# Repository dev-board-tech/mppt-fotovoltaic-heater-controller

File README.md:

# MPPT Fotovoltaic Heater Controller
 A compact fotovoltaic high power high voltage MPPT heater controller

A very compact heater controller that uses fotovoltaic panels in order to heat water in a boiler.

The project is developed around an Arduino nano V3 module using a BW OLED 128x64 SPI or TWI display.

The controller is designed to be configured working in BUCK or BOST mode thru changing the location of three jumpers.

The BUCK/BOST coil can be mounted externally using screws, the same the PV input capacitor, this allow for the board to be more compact decreasing the production price.

Include:

* One fan PWM output.
* Two onboard digital temperature sensors DS18B20.
* One wired NTC 10K temperature sensor wired to the heater.
* Onboard voltage reference TL431LP.
* Dedicated current sensor ACS758xCB-100B-PFF.
* One temperature exceeded output terminal.
* One RTC with backup battery because the controller is powered exclusively from panels DS1307.
* UART connector with 5V power.
* TWI connector with 5V power.
* Support three models of dedicated AC-DC/DC-DC inverter 95-385V to 9-12V for powering the board from panels HLK-PM12/HLK-5M12/RAC04-12SGA.
* BUCK inverter from 9-12V to 15-18V to efficiently drive the gate of the power MOS/IGBT MC34063AD.

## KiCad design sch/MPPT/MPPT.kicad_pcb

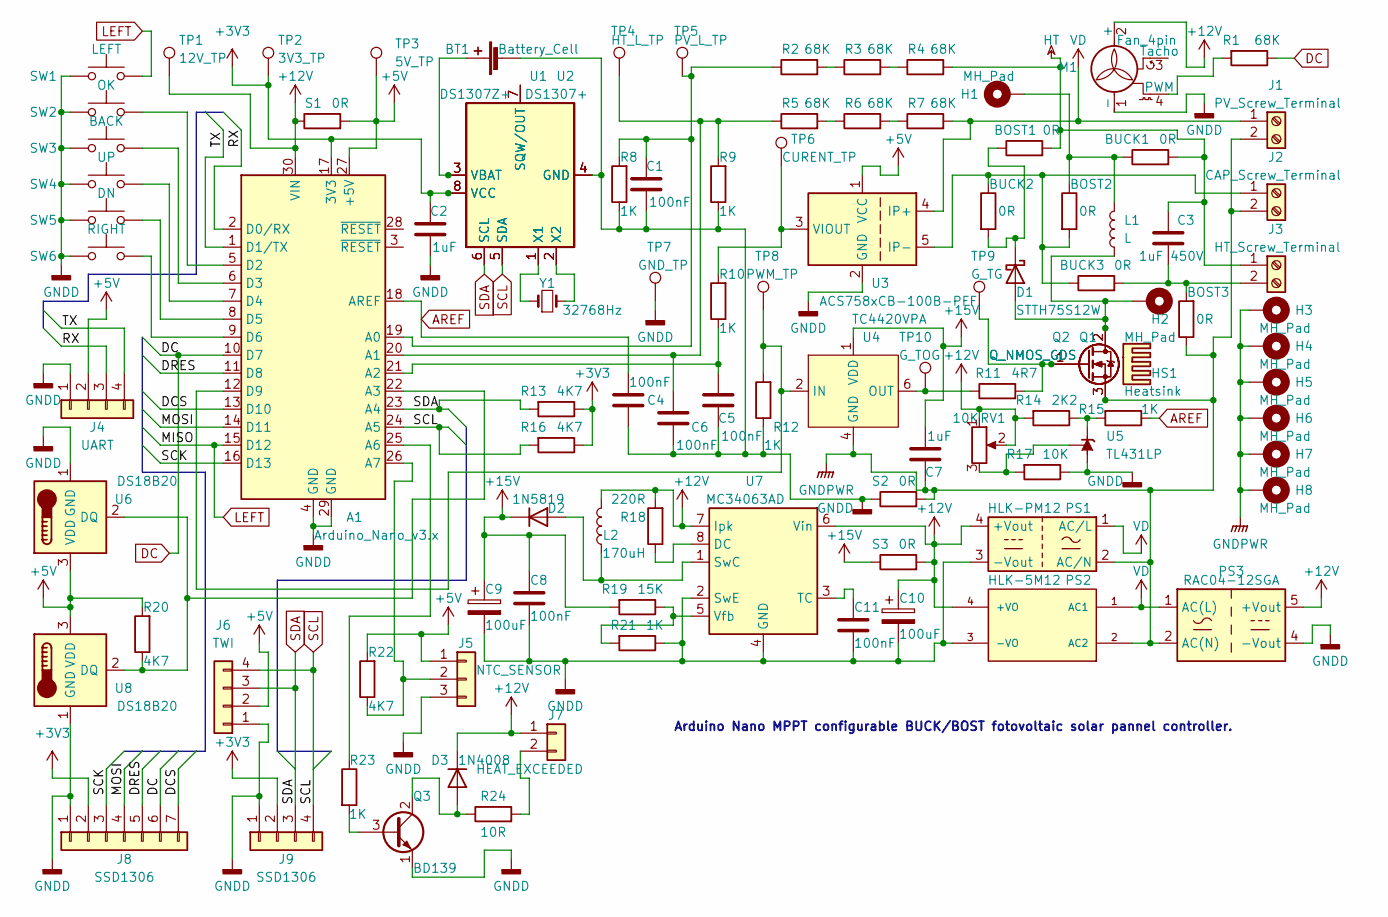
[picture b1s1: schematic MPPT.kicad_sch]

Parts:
A1: Arduino_Nano_v3.x; Arduino_Nano
BOST1, BOST2, BOST3: 0R; R_4020_10251Metric_Pad1.65x5.30mm_HandSolder
BT1: Battery_Cell; BatteryHolder_MPD_BC2003_1x2032
BUCK1, BUCK2, BUCK3: 0R; R_4020_10251Metric_Pad1.65x5.30mm_HandSolder
C1, C4, C5, C6, C8, C11: 100nF; C_0805_2012Metric_Pad1.18x1.45mm_HandSolder
C2: 1uF; C_0805_2012Metric_Pad1.18x1.45mm_HandSolder
C3: 1uF 450V; C_Rect_L27.0mm_W11.0mm_P22.00mm
C7: 1uF; C_1206_3216Metric_Pad1.33x1.80mm_HandSolder
C9, C10: 100uF; CP_Radial_D7.5mm_P2.50mm
D1: STTH75S12W; D_DO-247_Horizontal_TabDown
D2: 1N5819; D_A-405_P7.62mm_Horizontal
D3: 1N4008; D_A-405_P7.62mm_Horizontal
H1, H2, H3, H4, H5, H6, H7, H8: MH_Pad; MountingHole_3.2mm_M3_ISO14580_Pad_TopBottom
HS1: Heatsink; Heatsink_AAVID_TV5G_TO220_Horizontal
J1: PV_Screw_Terminal; TerminalBlock_MetzConnect_Type703_RT10N02HGLU_1x02_P9.52mm_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
J2: CAP_Screw_Terminal; TerminalBlock_MetzConnect_Type703_RT10N02HGLU_1x02_P9.52mm_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
J3: HT_Screw_Terminal; TerminalBlock_MetzConnect_Type703_RT10N02HGLU_1x02_P9.52mm_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
J4: UART; PinSocket_1x04_P2.54mm_Vertical
J5: NTC_SENSOR; TerminalBlock_bornier-3_P5.08mm
J6: TWI; PinSocket_1x04_P2.54mm_Vertical
J7: HEAT_EXCEEDED; TerminalBlock_bornier-2_P5.08mm
J8: SSD1306; PinSocket_1x07_P2.54mm_Vertical
J9: SSD1306; PinSocket_1x04_P2.54mm_Vertical
L1: L; HXX40A1.5uH
L2: 170uH; L_Radial_D10.0mm_P5.00mm_Fastron_07M
M1: Fan_4pin; Molex_SL_171971-0004_1x04_P2.54mm_Vertical
PS1: HLK-PM12; Converter_ACDC_HiLink_HLK-PMxx
PS2: HLK-5M12; CONV_HLK-5M05; PARTREV N/A
PS3: RAC04-12SGA; Converter_ACDC_RECOM_RAC04-xxSGx_THT
Q1, Q2: Q_NMOS_GDS; TO-247-3_Horizontal_TabDown
Q3: BD139; TO-126-3_Vertical
R1, R2, R3, R4, R5, R6, R7: 68K; R_1206_3216Metric_Pad1.30x1.75mm_HandSolder
R8, R9, R10, R12, R15, R21, R23: 1K; R_0805_2012Metric_Pad1.20x1.40mm_HandSolder
R11: 4R7; R_1206_3216Metric_Pad1.30x1.75mm_HandSolder
R13, R16, R20, R22: 4K7; R_0805_2012Metric_Pad1.20x1.40mm_HandSolder
R14: 2K2; R_0805_2012Metric_Pad1.20x1.40mm_HandSolder
R17: 10K; R_0805_2012Metric_Pad1.20x1.40mm_HandSolder
R18: 220R; R_0805_2012Metric_Pad1.20x1.40mm_HandSolder
R19: 15K; R_0805_2012Metric_Pad1.20x1.40mm_HandSolder
R24: 10R; R_Axial_DIN0204_L3.6mm_D1.6mm_P7.62mm_Horizontal
RV1: 10K; Potentiometer_Bourns_3296W_Vertical
S1, S2, S3: 0R; R_1206_3216Metric_Pad1.30x1.75mm_HandSolder
SW1: LEFT; SW_PUSH_6mm_H13mm
SW2: OK; SW_PUSH_6mm_H13mm
SW3: BACK; SW_PUSH_6mm_H13mm
SW4: UP; SW_PUSH_6mm_H13mm
SW5: DN; SW_PUSH_6mm_H13mm
SW6: RIGHT; SW_PUSH_6mm_H13mm
TP1: 12V_TP; TestPoint_THTPad_1.0x1.0mm_Drill0.5mm
TP2: 3V3_TP; TestPoint_THTPad_1.0x1.0mm_Drill0.5mm
TP3: 5V_TP; TestPoint_THTPad_1.0x1.0mm_Drill0.5mm
TP4: HT_L_TP; TestPoint_THTPad_1.0x1.0mm_Drill0.5mm
TP5: PV_L_TP; TestPoint_THTPad_1.0x1.0mm_Drill0.5mm
TP6: CURENT_TP; TestPoint_THTPad_1.0x1.0mm_Drill0.5mm
TP7: GND_TP; TestPoint_THTPad_1.0x1.0mm_Drill0.5mm
TP8: PWM_TP; TestPoint_THTPad_1.0x1.0mm_Drill0.5mm
TP9: G_TG; TestPoint_THTPad_1.0x1.0mm_Drill0.5mm
TP10: G_TOG; TestPoint_THTPad_1.0x1.0mm_Drill0.5mm
U1: DS1307+; DIP-8_W7.62mm
U2: DS1307Z+; SOIC-8_3.9x4.9mm_P1.27mm
U3: ACS758xCB-100B-PFF; Allegro_CB_PFF
U4: TC4420VPA; DIP-8_W7.62mm_LongPads
U5: TL431LP; TO-92_Inline
U6, U8: DS18B20; TO-92_Inline_Wide
U7: MC34063AD; SOIC-8_3.9x4.9mm_P1.27mm
Y1: 32768Hz; Crystal_AT310_D3.0mm_L10.0mm_Horizontal

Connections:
+3V3: A1.17 (3V3), C2.2, J8.2, J9.2, R13.1, R16.1, TP2.1, U1.8 (VCC), U2.8 (VCC)
+5V: A1.27 (+5V), J4.2, J5.1, J6.2, R20.2, R22.2, S1.2, TP3.1, U3.1 (VCC), U6.3 (VDD), U8.3 (VDD)
+12V: A1.30 (VIN), C10.1, D3.1 (K), J7.1, L2.2, M1.2 (+), PS1.4 (+Vout), PS2.4 (+VO), PS3.5 (+Vout), R14.2, R18.2, RV1.1, RV1.2, S1.1, S3.2, TP1.1, U7.6 (Vin), U7.7 (Ipk)
+15V: C7.2, C8.1, C9.1, D2.1 (K), R19.2, S3.1, U4.1 (VDD), U4.8 (VDD)
/DCS: A1.13 (D10), J8.7
/DRES: A1.11 (D8), J8.5
/MOSI: A1.14 (D11), J8.4
/RX: A1.2 (D0/RX), J4.3
/SCK: A1.16 (D13), J8.3
/TX: A1.1 (D1/TX), J4.4
AREF: A1.18 (AREF), C4.1, R15.1
DC: A1.10 (D7), J8.6, R1.1
GNDD: A1.4 (GND), A1.29 (GND), BT1.2 (-), C1.1, C2.1, C4.2, C5.1, C6.1, C8.2, C9.2, C10.2, C11.2, J4.1, J5.3, J6.1, J8.1, J9.1, M1.1 (-), PS1.3 (-Vout), PS2.3 (-VO), PS3.4 (-Vout), Q3.1 (E), R8.1, R9.1, R12.1, R17.1, R21.1, S2.1, SW1.1, SW2.1, SW3.1, SW4.1, SW5.1, SW6.1, TP7.1, U1.4 (GND), U2.4 (GND), U3.2 (GND), U5.2 (A), U6.1 (GND), U7.2 (SwE), U7.4 (GND), U8.1 (GND)
GNDPWR: BOST3.1, C7.1, H3.1, H4.1, H5.1, H6.1, H7.1, H8.1, J1.2, J2.2, PS1.2 (AC/N), PS2.2 (AC2), PS3.2 (AC(N)), Q1.3 (S), Q2.3 (S), S2.2, U4.4 (GND), U4.5 (GND)
HT: BOST1.2, BUCK1.2, C3.2, J3.1, R4.2
LEFT: A1.15 (D12), SW1.2
unnamed: A1.5 (D2), SW2.2
unnamed: A1.6 (D3), SW3.2
unnamed: A1.7 (D4), SW4.2
unnamed: A1.8 (D5), SW5.2
unnamed: A1.9 (D6), SW6.2
unnamed: A1.12 (D9), R12.2, TP8.1, U4.2 (IN)
unnamed: A1.19 (A0), C1.2, R2.1, R8.2, TP5.1
unnamed: A1.20 (A1), C6.2, R5.1, R9.2, TP4.1
unnamed: A1.21 (A2), C5.2, R10.1
unnamed: A1.22 (A3), R20.1, U6.2 (DQ), U8.2 (DQ)
unnamed: A1.25 (A6), R23.1
unnamed: A1.26 (A7), J5.2, R22.1
unnamed: BOST1.1, BUCK2.2, D1.1 (K)
unnamed: BOST2.1, BUCK1.1, H1.1, L1.2
unnamed: BOST2.2, BUCK2.1, BUCK3.1, J2.1, U3.5 (IP-)
unnamed: BOST3.2, BUCK3.2, C3.1, J3.2
unnamed: BT1.1 (+), U1.3 (VBAT), U2.3 (VBAT)
unnamed: C11.1, U7.3 (TC)
unnamed: D1.2 (A), H2.1, L1.1, Q1.2 (D), Q2.2 (D)
unnamed: D2.2 (A), L2.1, U7.1 (SwC)
unnamed: D3.2 (A), Q3.2 (C), R24.1
unnamed: J7.2, R24.2
unnamed: M1.4 (PWM), R1.2
unnamed: Q1.1 (G), Q2.1 (G), R11.2, TP9.1
unnamed: Q3.3 (B), R23.2
unnamed: R2.2, R3.1
unnamed: R3.2, R4.1
unnamed: R5.2, R6.1
unnamed: R6.2, R7.1
unnamed: R10.2, TP6.1, U3.3 (VIOUT)
unnamed: R11.1, TP10.1, U4.6 (OUT), U4.7 (OUT)
unnamed: R14.1, R15.2, U5.3 (K)
unnamed: R17.2, RV1.3, U5.1 (REF)
unnamed: R18.1, U7.8 (DC)
unnamed: R19.1, R21.2, U7.5 (Vfb)
unnamed: U1.1 (X1), U2.1 (X1), Y1.1
unnamed: U1.2 (X2), U2.2 (X2), Y1.2
unnamed: U1.7 (SQW/OUT), U2.7 (SQW/OUT)
SCL: A1.24 (A5), J6.4, J9.4, R16.2, U1.5 (SDA), U2.5 (SDA)
SDA: A1.23 (A4), J6.3, J9.3, R13.2, U1.6 (SCL), U2.6 (SCL)
VD: J1.1, PS1.1 (AC/L), PS2.1 (AC1), PS3.1 (AC(L)), R7.2, U3.4 (IP+)

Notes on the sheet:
Arduino Nano MPPT configurable BUCK/BOST fotovoltaic solar pannel controller.

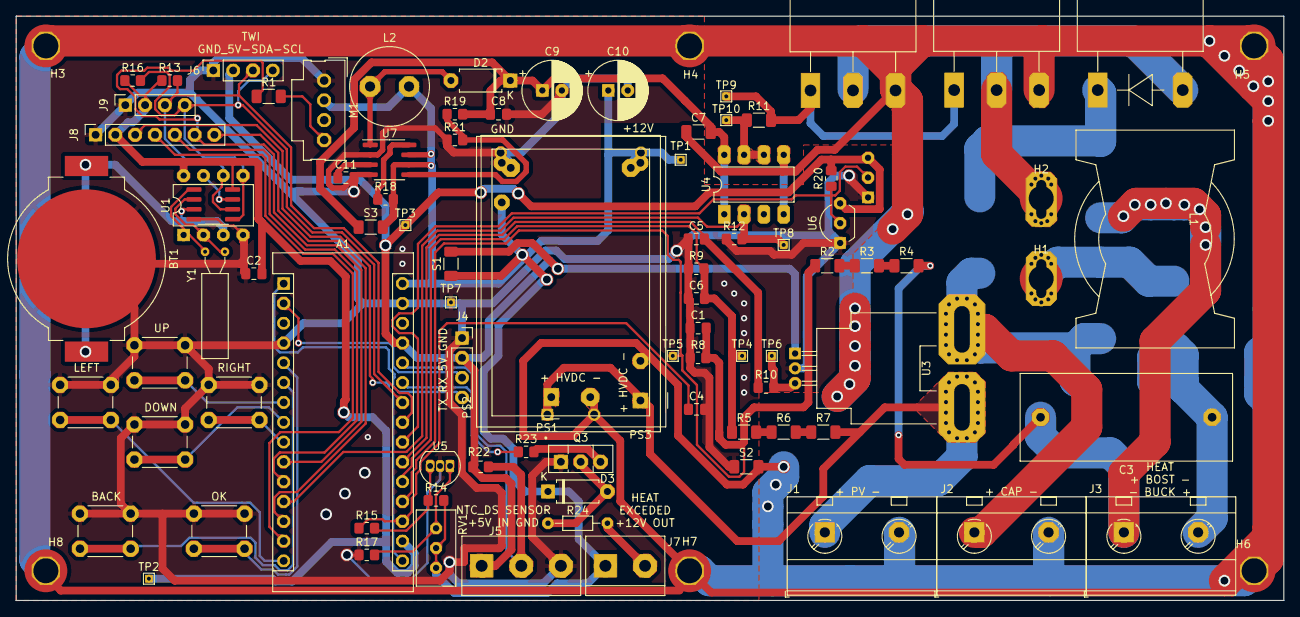
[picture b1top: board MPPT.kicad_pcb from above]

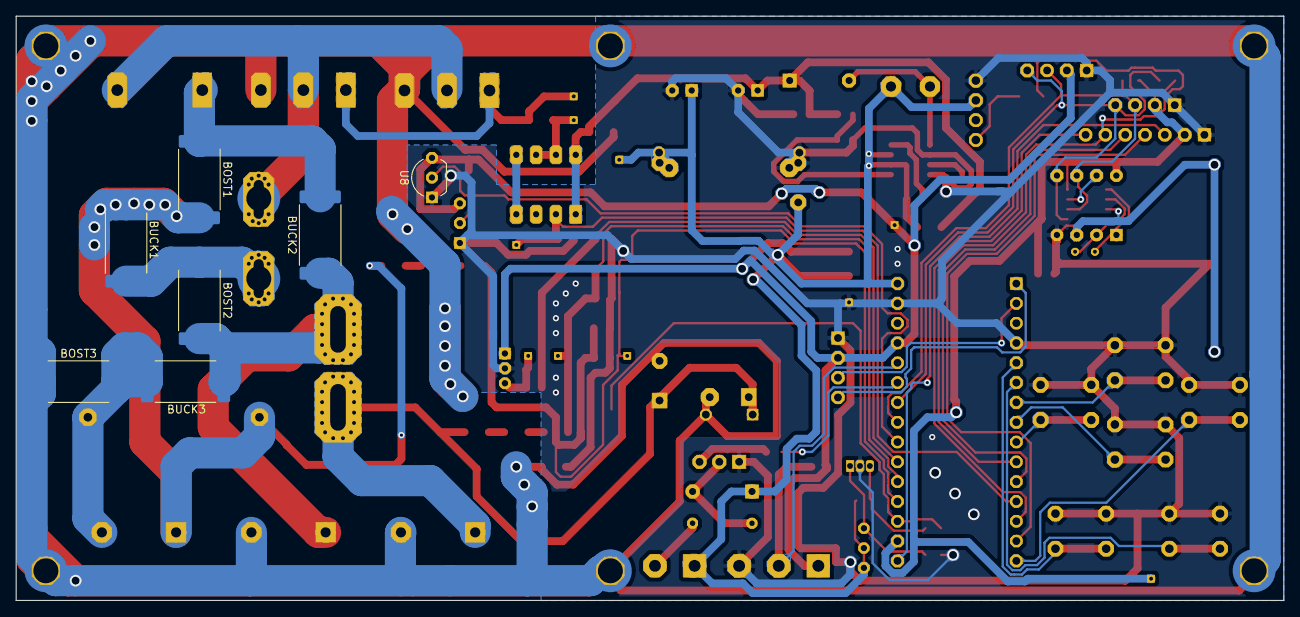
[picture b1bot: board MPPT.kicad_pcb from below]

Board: 2 copper layers, 162.6 x 74.9 mm, 102 parts (7 on the bottom side), 57 nets.

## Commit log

2022-08-29 First public commit
